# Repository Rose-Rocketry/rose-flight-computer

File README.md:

# Rose Flight Computer Firmware

This is the repository for the Rose Flight Computer's flight source code.

## Uploading Code

This project is intended to be uploaded to STM32 boards via SWD. Currently two
debugger devices have been tested: clone STLink debuggers and FreeDAP via RasPi
Pico. There is unfortunately no way to exempt individual parameters from the
configuration file from version control (that I know of) so you'll probably need
to change `platformio.ini` for your particular setup:
* For STLink (genuine or clones), use the following lines:
```
debug_tool = stlink
upload_protocol = stlink
```
* For FreeDAP, use the following lines:
```
debug_tool = cmsis-dap
upload_protocol = cmsis-dap
```

## Other useful links
Hardware design for this project:
<https://github.com/Rose-Rocketry/rose-flight-computer-hardware>

FreeDAP source repository:
<https://github.com/ataradov/free-dap>

FreeDAP Pi Pico breakout board:
link coming soon

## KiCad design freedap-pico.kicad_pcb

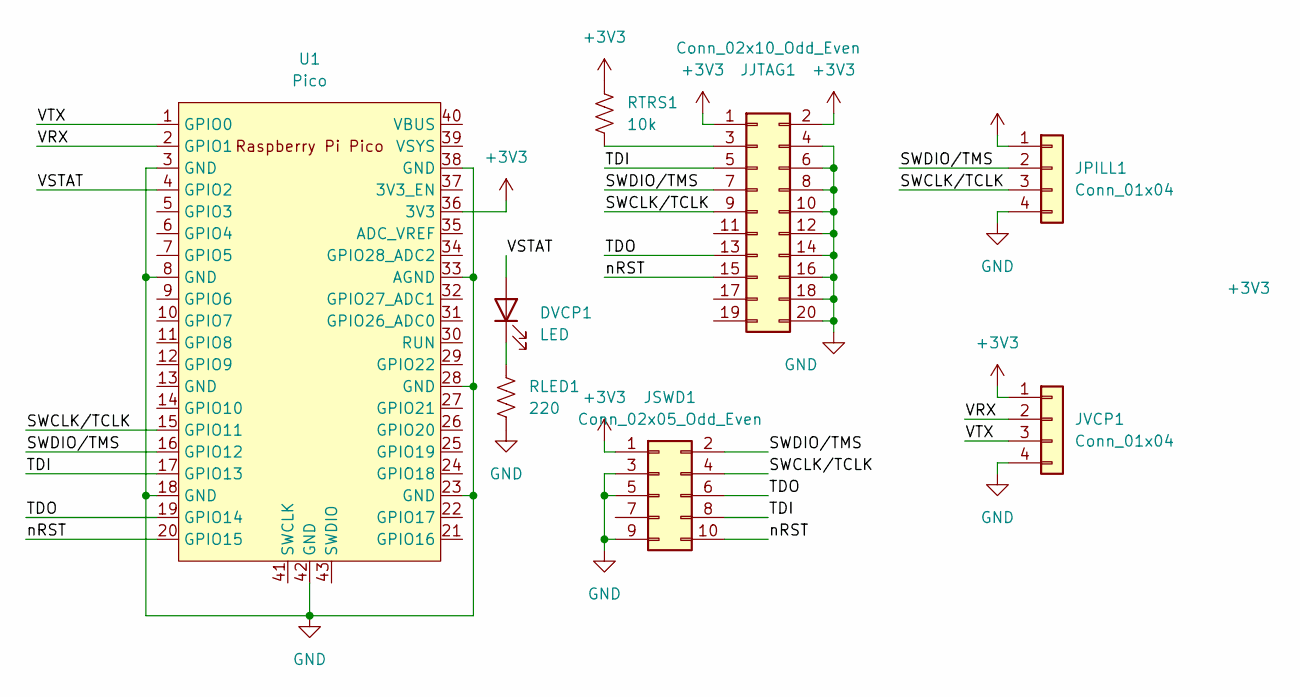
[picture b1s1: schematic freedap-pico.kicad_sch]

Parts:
DVCP1: LED; LED_D3.0mm
JJTAG1: Conn_02x10_Odd_Even; PinHeader_2x10_P2.54mm_Vertical
JPILL1: Conn_01x04; PinSocket_1x04_P2.54mm_Vertical
JSWD1: Conn_02x05_Odd_Even; PinHeader_2x05_P1.27mm_Vertical_SMD
JVCP1: Conn_01x04; PinHeader_1x04_P2.54mm_Vertical
RLED1: 220; R_Axial_DIN0207_L6.3mm_D2.5mm_P7.62mm_Horizontal
RTRS1: 10k; R_Axial_DIN0207_L6.3mm_D2.5mm_P7.62mm_Horizontal
U1: Pico; RPi_Pico_SMD_TH

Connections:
+3V3: JJTAG1.1, JJTAG1.2, JPILL1.1, JSWD1.1, JVCP1.1, RTRS1.1, U1.36 (3V3)
/SWCLK/TCLK: JJTAG1.9, JPILL1.3, JSWD1.4, U1.15 (GPIO11)
/SWDIO/TMS: JJTAG1.7, JPILL1.2, JSWD1.2, U1.16 (GPIO12)
/TDI: JJTAG1.5, JSWD1.8, U1.17 (GPIO13)
/TDO: JJTAG1.13, JSWD1.6, U1.19 (GPIO14)
/VRX: JVCP1.2, U1.2 (GPIO1)
/VSTAT: DVCP1.2 (A), U1.4 (GPIO2)
/VTX: JVCP1.3, U1.1 (GPIO0)
/nRST: JJTAG1.15, JSWD1.10, U1.20 (GPIO15)
GND: JJTAG1.4, JJTAG1.6, JJTAG1.8, JJTAG1.10, JJTAG1.12, JJTAG1.14, JJTAG1.16, JJTAG1.18, JJTAG1.20, JPILL1.4, JSWD1.3, JSWD1.5, JSWD1.9, JVCP1.4, RLED1.2, U1.3 (GND), U1.8 (GND), U1.18 (GND), U1.23 (GND), U1.28 (GND), U1.33 (AGND), U1.38 (GND), U1.42 (GND)
unnamed: DVCP1.1 (K), RLED1.1
unnamed: JJTAG1.3, RTRS1.2

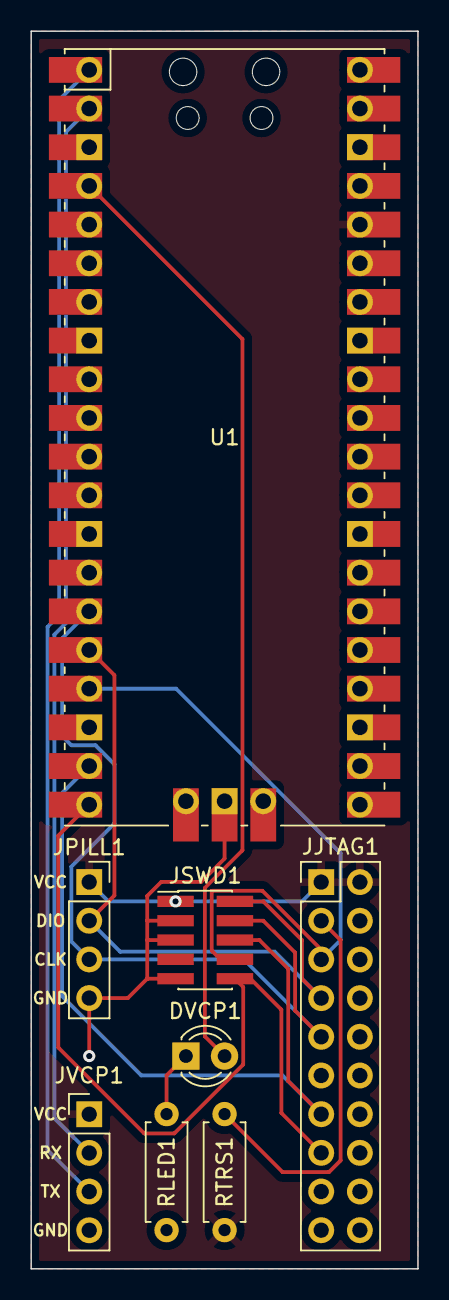
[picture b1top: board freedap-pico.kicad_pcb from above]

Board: 2 copper layers, 25.4 x 81.3 mm, 8 parts (0 on the bottom side), 12 nets.

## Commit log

2023-07-25 Moved dead reckoning to examples
2023-07-25 Updated library
2023-07-25 Cleaned up the mess somewhat
2023-09-29 Start of altimeter framework
2023-09-29 Update lsm lib
2023-09-29 temp
2023-09-29 Updated submodule
2023-09-29 Basic state stuff
2023-09-29 More basic framework
2023-09-29 Some documentation
2023-09-29 Fixed a typo
2023-09-29 Resolved merge
2023-10-01 Updated library; basics of accel data input
2023-10-01 Removed KiCad files accidentally added
2023-10-09 Broke out some parts to separate files
2023-10-09 Fixed gitignore; reworked some logging stuff
2023-12-20 I was a bad person and forgot to commit things forever
2023-12-20 I was a bad person, part 2
2023-12-28 More progress on fifos, still not particularly working
2024-01-29 Removed config/cache files
2024-01-29 Added .vscode to gitignore
2024-07-21 Switched from submodules to PlatformIO dependency manager
